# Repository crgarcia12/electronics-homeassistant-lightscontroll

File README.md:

# Home Automation Lights Controller - ESPHome & Home Assistant Compatible

A smart lighting controller PCB that integrates seamlessly with ESPHome and Home Assistant while maintaining full compatibility with traditional mechanical switches. This device acts as a "sidecar" to existing latching relays, adding smart home capabilities without compromising safety or requiring rewiring.

## Table of Contents

- [Overview](#overview)
- [Key Features](#key-features)
- [Quick Start](#quick-start)
- [Prerequisites](#prerequisites)
- [Available Versions](#available-versions)
- [How It Works](#how-it-works)
- [Installation Guide](#installation-guide)
- [Configuration](#configuration)
- [Technical Specifications](#technical-specifications)
- [Ordering from JLCPCB](#how-to-order-from-jlcpcb)
- [Development](#development-notes)
- [Version History](#version-history)
- [Contributing](#contributing)

## Overview

This circuit controls home lights following these core principles:

1. **Safe**: Safety is first and is not compromised in any decision
2. **Fail-safe**: If this device fails, the lights are still controllable using the mechanical switches
3. **Follows standard installation**: This device does not require you to rewire your house
4. **Centrally installable**: Can be installed in a central electrical panel

Following those principles and using as a reference a multi-switch light controlled with a mechanical latching relay, this is the wiring concept:

A normal circuit sends all push buttons to the latching relay, which controls the lights. This circuit (ESPHome) acts as a sidecar to the latching relay, functioning as a standard push button while also sensing the output of the latching relay to detect whether the lights are on or off.

## Key Features

### Hardware Features

- **Extensible design**:
  - Exposed I2C pins
  - Exposed Serial pins
  - Multiple GPIO pins available
  - 3.3V jumper: Allows disconnecting the internal ESP32 and replacing it with any other microcontroller
  - Relay pins (4-channel version): Relays can be controlled with an external microcontroller or device directly
  - Current sensing pins: Current sensing information is exposed for external microcontroller or device integration
  - Provides both 3.3V and 5V power rails
- **ESPHome compatible**: Easy integration with Home Assistant
- **Latest versions use ESP32-S3**: A powerful microcontroller with extensive features

### Safety Features

This device incorporates multiple layers of protection:

- Input fast-blow fuse
- Input MOV (Metal Oxide Varistor) for surge protection
- Slow fuses in every relay output
- Slow fuses in every mains detection input
- 4kV insulated power supply for low voltage isolation
- Conformal coating with 90kV/mm² insulation
- High-precision temperature sensor (SHT40)

## Available Versions

There are two main versions of the board:
- **4-channel version**: Compact design for smaller installations
- **8-channel version**: Extended capacity for larger installations

Latest versions use the ESP32-S3, which is a powerful microcontroller with WiFi, Bluetooth, and extensive GPIO capabilities.

## Quick Start

### What You'll Need

- One of the PCB versions (4 or 8 channels)
- Existing installation with mechanical latching relays
- WiFi network for ESPHome connectivity
- Home Assistant instance (optional, but recommended)

### Basic Setup Steps

1. **Order the PCB**: See [Ordering from JLCPCB](#how-to-order-from-jlcpcb) section
2. **Wire the device**: Connect to your existing latching relay setup
3. **Flash ESPHome**: Upload the ESPHome configuration (see [Configuration](#configuration))
4. **Integrate with Home Assistant**: The device will auto-discover in Home Assistant

For detailed instructions, see the [Installation Guide](#installation-guide) section below.

## Prerequisites

Before installing this controller, ensure you have:

- Basic understanding of electrical wiring and safety
- Existing mechanical latching relay installation
- Access to your electrical panel
- **Safety equipment**: Insulated tools, voltage tester
- **Knowledge**: Only qualified electricians should work with mains voltage
- ESPHome installed (for firmware flashing)
- Home Assistant (optional, for smart home integration)

## Current Version: Version 27

Version 27 is an evolution of version 26.1, optimized to fit perfectly in the standard DIN rail enclosure.

**Hardware**: Uses SN74LVCH8 level shifter with OUTPUT_ENABLED feature

## How It Works

### Mains Sensing
The PCB uses an optocoupler (LDA210 or ILD755) to detect the presence of mains voltage. These Darlington optocouplers are chosen specifically for their low current requirements, drawing only 0.7mA at less than 2V. This low-power design allows for efficient sensing without overheating components.

To reduce the mains voltage to a safe level for the optocoupler, a 300kΩ resistance setup is used. This configuration dissipates only 0.17W, which is split across two resistors. Each resistor, therefore, dissipates about 0.08W, preventing overheating issues commonly seen with other designs (such as those using the HCP chip). This improvement enhances both the safety and longevity of the PCB.

Each mains sensing channel is equipped with a fuse to protect against failures. In the event that one of the resistors fails short, the remaining resistor can carry up to 1.5mA until the fuse burns out, effectively preventing further damage. During this failure condition, the resistor would dissipate about 0.4W, so large resistors are used to withstand this potential load.

### Optocoupler and Capacitor Behavior

This PCB uses a Darlington optocoupler (LDA210), chosen for its high-gain behavior, which allows the system to react more quickly when mains power is turned on and requires less current on the LED side.

The oscilloscope images below show two different channels after the optocoupler while they are sensing mains. The yellow channel does not have any capacitors on the output, while the blue line has the capacitors.

In the first image, the optocoupler’s response to the sine wave is shown when mains power is ON. The blue line illustrates how capacitors help maintain the output in a high state when the AC cycle is crossing zero. This capacitor-induced holding effect ensures that the output remains stable, preventing fluctuations in the DC output that could cause false OFF triggers. However, this design means the line must be off for several cycles before the microcontroller can reliably detect the "off" state. Using excessively large capacitors can increase the detection delay to a noticeable extent, so capacitor size must be carefully selected to balance responsiveness and stability.

When mains power is first applied (yellow line), the capacitor requires time to charge before the optocoupler’s output reaches a high state (blue line). This results in a slight delay before the microcontroller detects the power-on state. If overly large capacitors are used, this delay becomes more pronounced, which can reduce responsiveness. The capacitor size must be carefully selected to minimize this delay while ensuring system stability.

Switching off mains power can generate noise, particularly depending on where in the sine wave the power is cut (e.g., at zero-crossing). Capacitors on the PCB help absorb much of this noise, reducing the likelihood of transient spikes or false "on" triggers that could interfere with other components or the microcontroller. This filtering helps improve system reliability, especially in noisy environments.

### Relays
The initial design for this system included small PCB-mounted mechanical relays, such as the PCN105D model. These relays, while compact and effective for basic switching, generated significant electromagnetic interference (EMI) due to the mechanical contacts. Despite efforts to mitigate this noise by adding flyback diodes and isolating the ground plane, the interference remained high. Under certain conditions, EMI levels were high enough to cause the microcontroller to reset, making this setup unreliable for stable home automation.

The image below illustrates the noise generated by the PCN105D mechanical relay during operation. This noise spike, especially during switching events, demonstrated the limitations of PCB-mounted relays in applications requiring low EMI.

These PCB relays are intended to trigger DIN-mounted latching relays, which are commonly used in electrical installations typically without flyback diodes, resulting in voltage spikes of several KV when switched off.

This picture shows PCN105D relays when switched off:

To address the noise and stability issues, the design was upgraded to use AQG22205 solid-state relays. These relays are only rated at 2A, but they incorporate an internal snubber circuit, making them far more resistant to voltage spikes on the mains side. Unlike mechanical relays, these solid-state relays do not generate any noise during switching.

## Installation Guide

> **⚠️ WARNING**: Installation involves working with mains voltage. Only qualified electricians should perform this installation. Improper installation can result in serious injury or death.

### Wiring Instructions

1. **Power off** all circuits at the breaker
2. **Verify** power is off using a voltage tester
3. Connect the controller to your existing latching relay setup following the wiring diagram above
4. Connect each mains sensing input to the appropriate circuit outputs
5. Ensure all connections are secure and properly insulated
6. **Double-check** all wiring before applying power

### First Power-On

1. Apply power to the device
2. The device should create a WiFi access point named "Hamodule Fallback Hotspot"
3. Connect to this access point and configure your WiFi credentials
4. The device will restart and connect to your network

## Configuration

### ESPHome Configuration

Example configuration files are provided in the
[`firmware/tester-code-esphome`](firmware/tester-code-esphome/) directory:

- [`EspHome.yml`](firmware/tester-code-esphome/EspHome.yml) - Basic 4-channel configuration
- [`EspHome-v22.yml`](firmware/tester-code-esphome/EspHome-v22.yml) - Configuration for version 22

#### Basic Configuration Example

```yaml
esphome:
  name: hamodule
  platform: ESP32
  board: esp32dev

wifi:
  ssid: "YOUR_WIFI_SSID"
  password: "YOUR_WIFI_PASSWORD"

api:
ota:

# Temperature sensor
sensor:
  - platform: sht4x
    temperature:
      name: "Temperature"
    humidity:
      name: "Relative Humidity"

# Light sensing and control
binary_sensor:
  - platform: gpio
    name: "Light 1 Status"
    pin: GPIO_PIN_NUMBER

switch:
  - platform: gpio
    name: "Light 1"
    pin: GPIO_PIN_NUMBER
```

### Home Assistant Integration

Once configured with ESPHome, the device will automatically be discovered by Home Assistant. You can then:

1. Go to **Settings** → **Devices & Services**
2. Look for the ESPHome integration
3. Click **Configure** on your device
4. Add it to your dashboard

Example floorplan integrations are available in the [`home-assistant`](home-assistant/) directory.

### ESP-IDF MQTT Firmware

The unified C++ firmware in [`firmware/lightcontrol`](firmware/lightcontrol/) supports the four-channel and
eight-channel boards. On first boot, connect to the `LightsSetup-XXXX` access point and open
`http://192.168.4.1` to configure WiFi, MQTT, room/device names, and the HTTPS firmware update URL.
Home Assistant discovers the light controls, firmware version sensor, and firmware update button through MQTT.
When an SHT40 is present at I2C address `0x44`, the firmware also publishes temperature and relative humidity
every 30 seconds. The onboard WS2812B on GPIO38 is exposed as a full RGB and brightness-controlled Home
Assistant light.

Configuration can instead be written directly over USB without using the setup access point. Store one
version-controlled JSON file per controller under
[`firmware/lightcontrol/provisioning/devices`](firmware/lightcontrol/provisioning/devices/). These files contain
the expected MAC address, WiFi SSID, MQTT broker/user, device name, room, and OTA URL, but never passwords.

Copy `secrets.example.json` to the ignored `secrets.local.json` and enter the shared WiFi and MQTT passwords:

```powershell
Copy-Item .\firmware\lightcontrol\provisioning\secrets.example.json `
  .\firmware\lightcontrol\provisioning\secrets.local.json
```

Then provision a connected controller:

```powershell
powershell -ExecutionPolicy Bypass -File .\firmware\lightcontrol\provision.ps1 `
  -Port COM3 `
  -ConfigPath .\firmware\lightcontrol\provisioning\devices\lightscontrol-36d4.json
```

The script verifies the connected ESP32 MAC, merges the tracked configuration with the ignored passwords,
flashes only the NVS partition, and deletes its temporary credential files. Missing secrets are requested
interactively instead of being added to the device configuration. `mqttPassword` can be shared by every
controller, or `mqttPasswords` can map each tracked MQTT username to a separate password.

The first OTA-capable image must be installed over USB because it introduces the dual-slot partition table.
Afterward, pressing **Install firmware update** in Home Assistant downloads the configured HTTPS image into
the inactive slot. ESP-IDF retains the previous image for automatic rollback if the new image cannot boot.
The Home Assistant **Firmware status** diagnostic reports each OTA phase and download percentage.
The RGB LED rapidly blinks purple while updating, then alternates blue and green during the reboot
connection sequence and turns off once WiFi and MQTT are healthy. The first update that installs this
behavior is still executed by the previous firmware, so purple indication begins with subsequent updates.
The separate active-high status LED on GPIO1 stays off and emits one brief pulse whenever an MQTT
message is published or received.

## Technical Specifications

### Circuit Simulation

If you want to understand how the mains sensing circuit works, you can use this simulation: [lushprojects circuit simulator](http://lushprojects.com/circuitjs/circuitjs.html?ctz=CQAgjCAMB0l3BWEBmGZkDYAcmte2AJwYYgDskISClCApgLRhgBQAbiA8Stp91pUoQaIAEyookmAhYB3EABYsIAYuVgFCqCwAma8JvBhRYyMpM66AMwCGAVwA2AF137RZE8xOizYkJdtHFz0mUh9lJQMtC2t7Z1dQ0wjzDz8AuJd5SPcTSNxtLOV8rlJ8yDlOMDDfRNQtcvkvJPAMSnCCytLIaNEtOu0AJz5SVUjVSlR4coAPEAxkZBQECDIRZAQtaMoAUQBlAAVkUQAdAGcAcX2ASQB5FgVIMkVs3wRRc19WeVFesQexX79cocVbeVKg5qCRQTaCLKHSCoYX7tDZbZTlIZI6Lgt5iVK0KYVVF-WiGHLaADGc2RvixeJMglgUwUhFZbPZHNIaDAZkwGh5ZiwZAoXKZXyoZNSdPJDWpaPIuPa5VO9OaC2q6MktgcpzoLExgJ8CpMRyhAsJ8mlUsNggqEPJENN2lmPkI4CwSAeWjAeEUphAAFkbABLAB2pzOuzo4bDAHNI7Jg04KQALCqaD5FTCQirk9pVNq+WUZkkA6L-coAe0kGHq0NZKCNMHgZCwxiQbUkyBY1bAT1rkgeDY7TLghDIGAQSKQEE8T271fEczrQ7dI6m48n0783kW3aAA).

<details>
<summary>Circuit simulation code</summary>

```
$ 1 0.000005 30.13683688681966 70 5 50 5e-11
v -96 368 -96 80 0 1 50 230 0 0 0.5
w 48 80 48 144 0
d 48 144 112 208 2 default
d 48 272 112 208 2 default
d -16 208 48 144 2 default
d -16 208 48 272 2 default
w 48 272 48 368 0
w 48 368 -96 368 0
w -16 208 -16 304 0
w 112 208 160 208 0
w -16 304 224 304 0
r -96 80 48 80 0 300000
x 633 351 750 354 4 20 ESP32\sGPIO
407 448 208 528 208 1
w 224 240 224 304 0
v 752 272 752 208 0 0 40 3.3 0 0 0.5
w 624 208 544 208 0
r 624 272 752 272 0 50000
w 544 240 544 272 0
c 624 208 624 272 0 0.0000049999999999999996 0.08913507182464649 0.001
w 544 272 624 272 0
w 624 208 752 208 0
s 272 208 336 208 0 0 false
r 624 320 752 320 0 1000000
w 624 272 624 320 0
w 752 272 752 320 0
x 209 185 404 188 4 20 Mains\sSensing\sSwitch
w 448 208 336 208 0
w 272 208 160 208 0
w 448 240 224 240 0
o 0 64 0 4099 320 0.00078125 0 2 0 3
o 17 64 0 4099 5 0.00009765625 1 2 17 3
o 23 64 0 4099 5 0.00009765625 2 2 23 3
```
</details>

## How to Order from JLCPCB

For detailed fabrication files and assembly instructions, see the [Development Notes](#development-notes) section below.

## Development Notes

## Generating fabrication files for JLCPCB
1. Plot PCB Gerber + Drill + Map:

1. Bom files

    Command: python3 "C:\Program Files\KiCad\bin\scripting\plugins/bom_csv_jlcpcb.py" "%I" "%O.csv"

1. Drill files

    run the python script to rotate the components

    PS C:\\...\smt-assembly> python3 .\kicad-to-jlcpcb-pos.py .\hamodule-top-pos.csv .\hamodule-top-pos-jlcpcb.csv

### Generate Documentation

**Schematics:**

**PCB:**
Print to PDF, and use a high-resolution PDF to JPG converting website like: https://pdf2jpg.net/

---

## Version History

This section documents the evolution of the board design through multiple iterations.

### Older Versions: 26.1, 26.2, 26.3 - Eight Channels with IO Expander
**Changes compared to version 23:**
- Using TCAL6416A instead of MCP23108 due to having push-pull instead of open-drain outputs
- MCP23017 has released an amendment to the datasheet declaring a bug in two pins, making them read-only
- Adjusted the border cut-outs to fit the middle mounting hole
- Fixed a bug in the TXB0108 implementation: OE and DIR pins should reference VccA (requires voltage divider: VccA = 3V, not 3.3V)
- Added descriptions in the schematics
- Created 3 subversions by JLCPCB to test fitting in the case (all the same circuit, different board sizes)
- **Known Bug**: The resistors R27-R34 are too weak because the 74LVCH8T245PWE4 level shifter has bus voltage holder

Version 26.1 (SN74LVCH8 + OUTPUT_ENABLED)

### Older Versions: 24 - Eight Channels with IO Expander

**Changes compared to version 23:**
- Using TCAL6416A instead of MCP23108 due to having push-pull instead of open-drain outputs
- MCP23017 has released an amendment to the datasheet declaring a bug in two pins, making them read-only
- Adjusted the border cut-outs to fit the middle mounting hole
- There are two versions of this board: one using SN74LVCH8 and the other one using TXB0108. To compare them, switch between the two schematics in two browser tabs

Version 24.8-1 (TXB0108)

Version 24.8-2 (SN74LVCH8 + OUTPUT_ENABLED)

### Older Versions: 23 - Eight Channels

**Changes compared to version 22:**
* Eight channels controlled via I2C for relays and mains sensing
* Added RGB Led controller
* Capacitor for 5v line
* Compatible with case: RS PRO Modular Enclosure for DIN rail Stock number: 1862291 (https://uk.rs-online.com/web/p/din-rail-enclosures/1862291/)
* Added MCP23018 as IO expander and TXB0108PW to shift the output of the Darlington (~2.5V) to the logical high (3.3V)

Bugs
* MCP23018 is open drain and not a direct replace from MCP23017: Outputs are GND or disconnected, not Vcc
* Mid-PCB mounting hole in the cut version is not properly placed

### Older Versions: 22 - Four Channels
[Detailed information](PCB/schematics-v22-jlcpcb/)

**Changes since Version 17:**
- Cut-out ESP32 antenna area
- Moved silkscreen for better readability
- Improved schematic readability
- Added LEDs to indicate when relays are ON

### Older Versions: 21

**Key Changes:**
- Using the new ESP32-S3 microcontroller
- Replaced CP2102 with ESP integrated USB support
- Replaced USB protection diodes with an IC

### Older Versions: 20
[Detailed information](PCB/schematics-v20-pcbway/)

**Changes since Version 17:**
- Mains sensing is inverted to make better use of rectifier capacitors and have constant reading
- Removed low-voltage fuse (having only one fuse is sufficient since PS has overcurrent protection and >4kV insulation)
- Moved screws - now has one extra holding point
- Exposed GPIO12 and GPIO33 for better board extensibility
- Moved to SSR with integrated snubber instead of mechanical relays (the kickback of the inductive load from latching relays was creating spikes and restarting the ESP32)
- Added SMD capacitors to the 3.3V and 5V lines for noisy conditions
- Separated GND for relays and ULN from the digital signal plane to reduce noise 

### Older Versions: 19
[Detailed information](PCB/schematics-v19-jlcpcb/)

**Changes since Version 17:**
- Added fuses to every relay output (protection in case two relays are closed simultaneously and one is accidentally wired to N - current could flow from one to the other)
- Moved SHT40 and extended the footprint for easier soldering
- Moved LD11 for easier fitting in the case
- Tested with both optocouplers: LDA210 and ILD755-D

### Older Versions: 17
[Detailed information](PCB/schematics-v17-safety-jlcpcb/)

**Major changes since Version 13:**
- Changed optocoupler to one with lower current requirements
- Changed resistors to 150kΩ × 2
- Added fuses to every sensing channel and removed fuse in N
- Added a separate fuse for 5V and 3.3V track
- Littlefuse now has a holder instead of being soldered directly to PCB
- Added ESP32 onboard module
- Added temperature sensor to detect if the board gets too hot
- Added USB-C powered by CP2102N UART chip
- Removed capacitors from 5V→3.3V converter to avoid inrush current at the USB
- Added external pull-up resistors for ESP32 (some pins do not have internal pull-ups)
- Added mains nets with proper creepage and clearance
- Replaced mains connectors with Wago lever connectors (super reliable and easy to use!)
- Replaced analog temperature sensor with SHT40 using I2C protocol
- Added I2C terminal so any I2C sensor can be plugged in

The enclosure compared with a DIN relay. Size is perfect :)

### Older Versions: 16
Size comparison between V16 and V13:

### Older Versions: 13

**Miniaturization improvements:**
- Using SPST-NO 3A smaller relays
- Using SMD 3W 29kΩ resistors instead of THT
- Removed external buttons connector
- Removed external LEDs connector
- Using SMD ULN2003A instead of THT
- HCPL3700 THT capacitors replaced by Tantalum SMD

**Security additions:**
- Added fuse at the neutral return from the sensors (F2)
- Resistors are placed before HCPL3700 to work with less than 4V to N instead of 110V to N

**Stability improvements:**
- Added filter capacitor to ULN2003A
- Added filter capacitors to LD1117AV33

**Other changes:**
- Added LED indicator when powered on

### Older Versions: 9

Early development version. 

### Older Versions: 1

Initial prototype version (included to show the evolution of the project). 

---

## Contributing

Contributions are welcome! If you have improvements, bug fixes, or new features to propose:

1. Fork the repository
2. Create a feature branch (`git checkout -b feature/your-feature`)
3. Make your changes
4. Test thoroughly (especially if working with mains voltage)
5. Submit a pull request with a clear description of your changes

**Please note:** Any contributions involving electrical safety must be thoroughly tested and documented.

## Safety Disclaimer

⚠️ **WARNING**: This device works with mains voltage which can be lethal. Only qualified electricians should install, modify, or work on this device. The authors assume no liability for any damage, injury, or death resulting from the use of this device. Use at your own risk.

## License

This project is open source. Please check the repository for specific license information.

---

## Support

For questions, issues, or discussions:
- Open an issue on GitHub
- Review existing issues and documentation
- Check the ESPHome and Home Assistant communities for integration help

---

**Project maintained by the community. Star ⭐ this repository if you find it useful!**

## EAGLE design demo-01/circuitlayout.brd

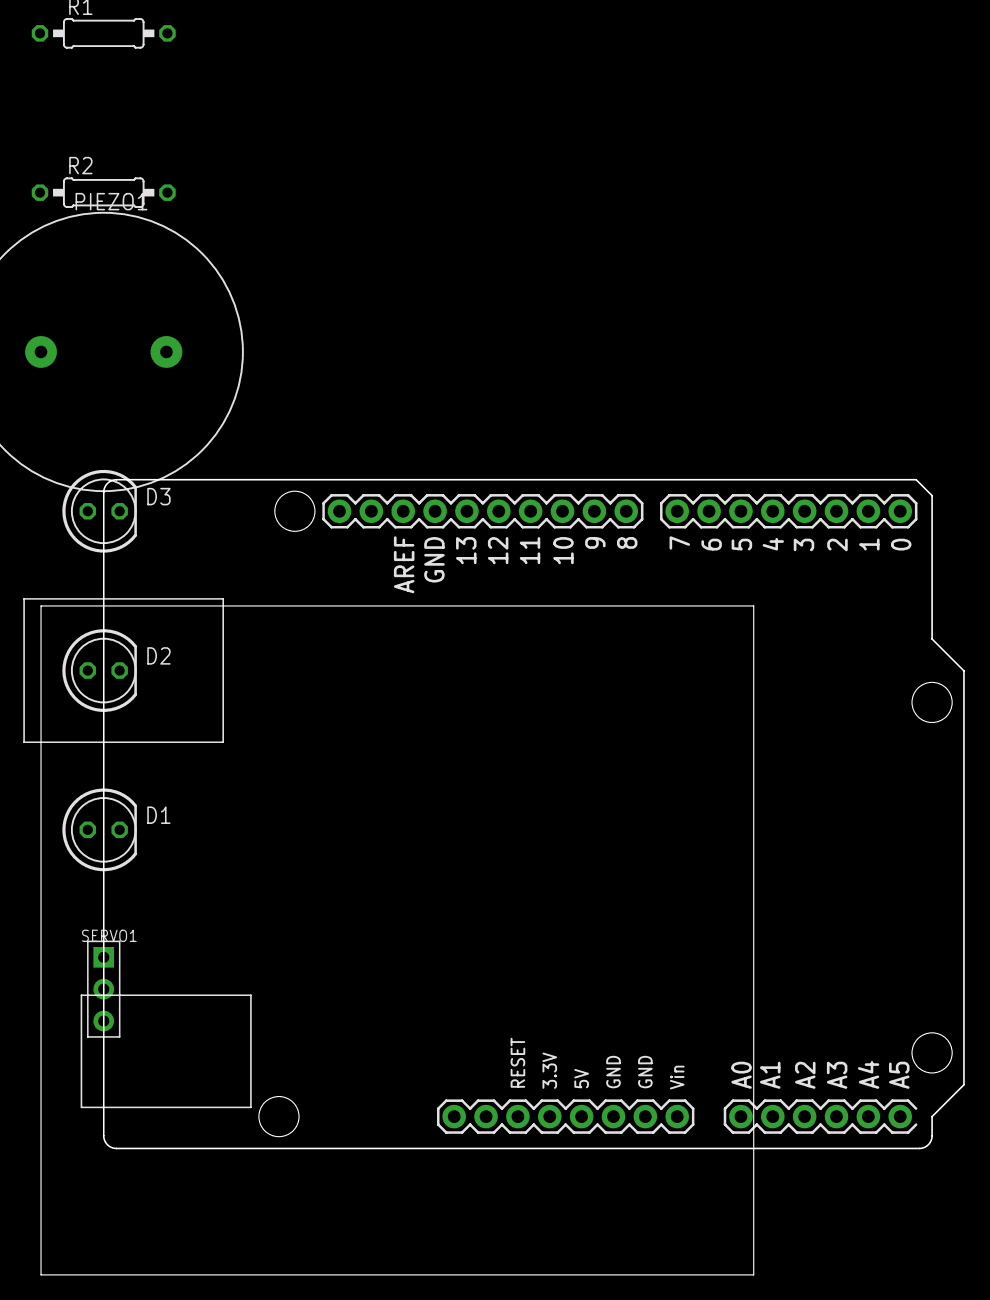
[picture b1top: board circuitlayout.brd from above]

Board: 2 copper layers, 73.6 x 63.4 mm, 8 parts (0 on the bottom side), 9 nets, no tracks yet.

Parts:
D1, D2, D3: LED5MM
PIEZO1: PIEZO-22MM
R1: 330‎Ω; 0207/10
R2: 1k‎Ω; 0207/10
SERVO1: 1X3P-2.54-2.54-11.6-3.0-BLACK-MALE
U1: ARDUINO_UNO

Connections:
unnamed: SERVO1.3, U1.9
unnamed: D1.A, U1.7
unnamed: D2.A, U1.6
unnamed: D3.A, U1.5
unnamed: D1.K, D2.K, D3.K, R1.2
unnamed: SERVO1.2, U1.5V
unnamed: R2.1, U1.10
unnamed: PIEZO1.P$1, R2.2
unnamed: PIEZO1.P$2, R1.1, SERVO1.1, U1.GND..

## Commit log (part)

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2020-08-26 string and menu works
2020-08-26 encoder -nowork
2020-08-26 works :)
2020-08-30 Readme updates
2020-08-30 adding some schematics
2020-08-31 ready for pcb
2020-08-31 pcb ready
2020-09-01 work on pcb and fix readme
2020-09-03 new way
2020-09-04 adding debug variable
2020-09-14 works hello world
2020-09-17 cleaning project
2020-09-17 removing build folder
2020-09-17 removing demo 7
2020-09-17 encoder works!
2020-09-20 adding button
2020-09-20 ultrasonic works
2020-09-20 closer, but errors in sprintf
2020-09-27 refresh faster
2020-10-05 adding PCB
2021-04-01 adding ws2815 led strip demo
2021-08-02 demo 8 + esp_from_windows
2021-08-24 adding some docs on ESPHome.yaml
2021-08-24 adding docs
2021-08-28 initial ESPHome device
2021-08-29 finished v1
2021-09-05 esphome module
2021-09-05 adding new 11.4
2021-09-05 adding HCPL3700 circuit
2021-09-06 using HCPL3700
2021-09-07 some changes to schema
2021-09-12 updating caps & resistor
2021-09-18 schematics v7
2021-09-19 arranging 22v sensing
2021-09-19 varistor + F.SilkS
2021-09-20 adding caps
2021-09-20 caps are wrong way around
2021-09-20 mounting holes + text correction + ...
2021-09-20 adding pins to mesure current
2021-09-25 adding unfinished v8
2021-09-26 order to jlcpcb
2021-10-02 readme
2021-10-02 something went wrong with renaming demo 5. too old to take a look at it
2021-10-05 jlcpcb v2: increas connectors pads + fix numbering for sensors in labels
2021-10-06 adding an output fuse
2021-10-06 gerber - new fuse
2021-10-24 notes and reorganizing
2021-10-24 2 resistor + jlcpcb
2021-10-31 gebert + bom
2021-11-01 adding caps here and there
2021-11-11 cleaning tags
2021-11-13 sent to JLPC
2021-11-21 removing all other demos, and sorting folder
2021-11-22 updating readme + adjust value in jlpc schematics
2021-11-23 added new version
2021-11-23 adding thermal pad behind resistors
2021-11-23 adding thermal vias
2021-11-30 half way with new optocouplers
2021-12-03 removing vias
2021-12-05 adding an embeded ESP to the PCB
2021-12-05 fixing rules, missed connections, GND plane
2021-12-06 adding V3 readme
2021-12-06 adding readme inside kicad folder
2021-12-27 using the right USB connector. We need Mode B
2021-12-27 copying USB part from DevKit, adding missing caps, 0Ohm resistors for TXRX
2021-12-29 adding temp sensor + Serial pins
2021-12-31 updated part number
2022-01-02 new routing
2022-01-04 fab files for v16
2022-01-16 README + fab files
2022-01-16 changed big caps + readme + routing + JLCPCB
2022-01-17 adding some docs
2022-01-18 temp sensor caps + disconnect shield
2022-01-18 Kicad6
2022-01-28 adding usb-c, reduce D+/- lenght, broke d View :(
2022-01-30 updating libraries to kicad6. some footprints got bigger :S
2022-02-02 fixing kicad6 library reference. Using the right transistor package. Fixing 3D for some components
2022-02-02 adding gerber + BOM + new images for README
2022-02-02 adding missing resistors to the USB port
2022-02-04 fixing EspRel wrong naming
2022-02-06 fixing electrolytic Capacitor values
2022-02-06 temp sensor GPIO is not compatible with Wifi! Crap, I should have tested this
2022-02-07 routing some things nicer
2022-02-24 adding fulses to the sensing lines
2022-02-24 adding production files
2022-02-24 fixing ERC errors
2022-02-25 move USB to upper side, and JLCPCB part. Fix netlits for mains + clearance
2022-02-26 updating main readme
2022-02-26 switched 3.3v jumper after the JST. This allow disconnecting the onboard ESP, and connect an external one
2022-02-26 adding Depsi! :)
2022-02-27 make silkscreen nicer
2022-02-28 TempSensor traces + fix 3D for buttons + remove board review
2022-03-01 add bom generator script + fab-files + silkscreen
2022-03-02 removing unused files
2022-03-14 fixing nets clearance + re-routing N through high voltage area + moving relays
2022-03-15 readme + clearance image
2022-03-15 adding clearance image to readme
2022-03-15 adding more explanations to clearance
2022-03-15 adding missing title to readme
2022-03-20 mains class is 1.5mm clearance
2022-03-20 fab files
2022-03-20 updating back picture
2022-03-21 3D img no components + PcbWayBom
2022-03-31 rerouting some 5V + adding slots + fixing net
2022-04-02 sorting BOM components
2022-04-02 rename folder - update Readme
2022-04-02 adding v18
2022-04-02 fixing readme v17 links in main readme
2022-04-06 minor changes
2022-05-09 [BUG] v17 - R11 lowers V too much and ESP cannot be programmed. Replacing by 0Ohms to not to change layout (removed in future versions)
2022-05-10 [V17][BUG] Updating the readme with the latest schematic image, showing the fix of the USB resistor bug
2022-05-13 reversing versions in Readme. Newer first
2022-05-30 flipping SHT40 and adding bigger pads for easier soldering
2022-05-30 adding instructions on jlcpcb
2022-05-31 Updating JLCPCB how to order
2022-06-03 fuse 3d model + updating readme images
2022-06-03 moving GH URL + adding real pictures + Readme
2022-06-03 [V18] updaing readme.md with system conncetion image from V18
2022-06-03 [V18] Adding all v18 images to main readme
2022-06-04 creating V19
2022-06-04 sent v19 to jlcpcb
2022-06-04 [V19] images + 3d model for fuses
2022-06-04 updating readme to V19
2022-06-05 updating readme
2022-06-06 Readme + ESPHome config file
2022-06-15 ESPHome pin correction + Arduino test code
2022-07-11 Creating V20
2022-07-11 added 5v selector between USB and PS
2022-07-31 adding oscilloscope images for sensing
2022-07-31 [Readme] Mains sensing
2022-08-02 saving oscilloscope screenshots
2022-08-03 adding setup photos
2022-08-14 adding idf tester code; moving arduino code
2022-08-15 adding some relay trigger code
2022-08-18 changing relays to AQG12205
2022-08-23 adding caps, SSRelays
2022-08-23 adding ci-cd
2022-08-23 ci-cd
2022-09-18 [V20] Move Earth;arrange minors;prod files
2022-09-18 [V20] ERC rules for schematics
2022-09-18 [V20] schematics diagram
2022-09-18 updating readme images
2022-09-21 routed neutral; silkscreen; new images; prd files; remove testing files
2022-09-21 [V20] readme images;
2022-09-24 [V20] README ; Rename folder to PcbWay
2022-09-25 [V20] Fixing relays 3D in PCBNew. Nothing changed on the PCB itself
2022-09-25 [V20] oscilloscope img + readme
2022-10-04 Adding Esp32 S3 support
2022-10-04 [V21] Bring DEPSI back!; expose 3rd GPIO; remove ESP unused libraries;
2022-10-27 renaming v21. It was sent to production
2022-10-27 adding version 22, with cut out
2022-12-05 improving schematics, removing global variables and use wires instead to make it clear how the circuit is working; trying to move inputs to the left, output to the right
2022-12-05 update board schematics image - easier to read
2022-12-05 [V22] Updated image of schematics
2023-02-01 adding leds to indicate relays operation
2023-02-08 Use VBus for ESD before BAT diode; Adding 2 more GPIO; Adding more caps
2023-02-08 rename V22 to V22-jlcpcb
2023-02-08 [v22] updating readme images
2023-02-13 testing changes
2023-02-14 more changes
2023-04-19 Adding real images of the board
2023-04-19 fixing readme image file extension
2023-05-08 fixing Readme
2023-05-29 [V23] In progress: 8 channels solution
2023-05-29 upgrade ready to kicad 7.05 for v23.4 and v23.8
2023-06-05 pointing action to V7 23.4
2023-09-26 [V8] adding indicators for 5 and 3.3 V
2023-09-26 [V8] fixing switch silkscreen
2023-09-30 [V23.8] Adding screen connector + Fixing version + adding caps
2023-11-01 fabrication outputs for v8
2023-11-01 updating pipeline
2024-05-28 setting up for a new case
2024-05-28 fixing power sockets (3.3v and 5v) + prod files + readme
2024-05-28 reducing board size
2024-05-28 README.md
2024-05-29 minor fixes
2024-05-29 adding silkscreen to J13
2024-08-06 fixing some checkrules
2024-08-07 order from JLCPCB
2024-08-09 replaccing NC caps by caps with value, and adding notes in schematics
2024-08-11 extend gnd plane
2024-08-11 adding spare components
2024-08-19 adding simulations to validate
2024-08-21 Using shift level converter to drive MCP
2024-08-24 [v23.8] sent to jlcpcb
2024-08-24 sent to jlcpcb
2024-09-08 24.8 checked in by accident
2024-09-08 Adding version 24
2024-09-09 ordered 24 to jlcpcb
2024-11-08 Fix ESPHome configuration file for TCAL6416A
    ---
    For more details, open the [Copilot Workspace session](https://copilot-workspace.githubnext.com/crgarcia12/electronics-homeassistant-lightscontroll?shareId=XXXX-XXXX-XXXX-XXXX).
2024-11-08 [24.1] Adding board and schematics
2024-11-08 changing readme to include 24.1 and 24.2
2024-11-09 [v24] adding explanation on why two V24 versions (TXB0108 vs SN74LVCH8)
2024-11-14 Adding version 25
2025-05-04 fixing issue caused by Kicad8. Kicad 9 with many ERC fixed
2025-05-06 pull-up for TCAL. Fix ERC. Fix 3D models. Fix Silkscreen
2025-05-07 update kibot settings
2025-05-27 Adding GND vias close to signal. Separate signal vias to make sure that they dont create a large cut in layer 2 and 3. For example for the LEDs going to ULN or the R56, R57, etc. Their vias are not a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
2025-05-27 Changes in the schematic look: 1. Align label text to the right, in order the trace is under the label. 2. Display resistors values for the resistors next to the LED (R45... R5x) 3. Align the identif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
2025-06-02 adding ground vias close to signal vias going to ULN2803. Adding Power supply model to silkscreen
2025-07-22 Adding v26
2025-07-22 areas were not properly filled in PCB
2025-07-22 update GH Action to point to the latest board
2025-08-02 [V26] Rearranging some nets. Fixing some connections that were missing. Solving some ERC. Updating UL28003 footprint to match current library
2025-08-04 [V26] Updated RST-80-AMMO (lib -> kicad_sym). Updated components to match library naming <library:footprint>. Utilize standard library for some components (SHT40, ULN). Updated LD1117 symbol to match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
2025-08-04 Fixed library filters to allow selected footprint
2025-08-04 Created only one project specific symbol library, one for footprints, and one for icons. Deleted all the rest from the components folder
2025-08-05 Created symbols for every image and logo, in order there are no warnings
2025-08-05 Adding new spare part: C50 - 0402 capacitor
2025-08-14 change large 3.3v capacitor orientation. Fixed SNT IC silkscreen. Moved TP on data line to avoid GND plane breaking
2025-08-14 renaming 26.8 to 26.1 - numbering will be used for different board sizes to test fit in the enclosure
2025-08-14 [V26] deleted outdated production files
2025-08-15 fixing wrong path in GH Action kibot.yaml
2025-08-15 GH Actipon Jlcpcb is imported by the main kibot config
2025-08-15 changing kibot upload path
2025-08-15 [V26] [Kibot] Updaring old preflight checks ( erc and drc ) - deleting some unused documents (PCB in red, blue, etc)
2025-08-19 Adding 26 2L. This is a version used only to test fit of the PCB on the case. All v26 will be like that. The main difference is the production files
2025-08-19 Adding v 26.2. This is the same as V26.1. In the next commit, it will have a smaller board. to test fit in the case.
2025-08-21 Adding V 26.3, copied from 26.2
2025-08-21 Version 26.3
2025-10-12 adding store tester code
2025-10-12 updating store tester code
2025-10-12 renaming schematics-v26.2 to schematics-v26.2-jlcpcb
2025-10-12 renaming schematics-v26.3 to schematics-v26.3-jlcpcb
2025-10-12 [V27] Adding version V27. Updaring Readme
2025-10-13 [V27] Trying to fix the pipeline
2025-10-13 Fixing GH Action: type: pcbdraw does not support layers selection anymore
2025-10-16 tcal demo in idf compiles, but it does not worki
2025-10-18 it works :) I was using port 0 as output, but it is port1
2025-10-20 deleted idf blink examples, now that the tcal example works
2025-10-20 it works with the new library
2025-11-26 moving to Cpp. not tested
2025-11-27 [v27] uses now 1k resistor as pull down for TCAL read port. Updated schematic and PCB with V27
2025-12-05 Initial plan
2025-12-05 Comprehensive README improvements: structure, content, and formatting
2026-02-08 Add Spanish translation of README (README.es.md)
2026-06-26 [v27] updated to the latest kicad version v10
2026-06-26 [v27] Fix USB-c schematic does not match footprint Rule error
2026-06-27 updating the version. updating part numbers for jlcpcb
